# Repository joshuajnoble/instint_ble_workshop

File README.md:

instint_ble_workshop
====================

This is for a workshop I ran at instint 2014 and it has a bunch of components to it:

board: eagle files that I created for the board that we used.
ios: openframeworks applications for running on a BLE compatible IOS device
osx: openframeworks applications for running on a BLE compatible OSX device
processing: processing applications for running on a BLE compatible Android device
rfduino: applications that running on the RFDuino BLE platform

In the workshop we used a few different components:

* https://www.sparkfun.com/products/8680	SoftPot Membrane Potentiometer - 50mm
* https://www.sparkfun.com/products/9873	FTDI Basic Breakout - 3.3V
* https://www.sparkfun.com/products/9264	LED - RGB Diffused Common Cathode
* https://www.sparkfun.com/products/11026	Jumper Wires Standard 7\" M/M Pack of 30
* https://www.sparkfun.com/products/12002	Breadboard - Self-Adhesive (White)
* https://www.sparkfun.com/products/11446	Triple Axis Accelerometer Breakout - ADXL362

And here's what these different applications in the different platforms do:

* sayhi - just says hi back and from the RFDuino to the host device
* changeLED - sends an LED signals to the RFDuino to control an RGB LED
* receiveAcc - receives a accelerometer signal from the rfduino and moves a little ball around on the screen (pretty dull tbh)

There's another one that only run on the RFDuino:

* customID - runs on a device and sends a message to another device
* customIDdevice - runs on a device and sends a message to another device

I have a hacked RFDuino install, so drop that in your Arduino (or Arduino.app) hardware/arduino folder. I also have a hacked Processing Android mode, so drop that in your Processing/modes folder to leverage features in more contemporary Android releases (i.e. v18+). Any questions or problems just open an issue and I'll get back to you ASAP

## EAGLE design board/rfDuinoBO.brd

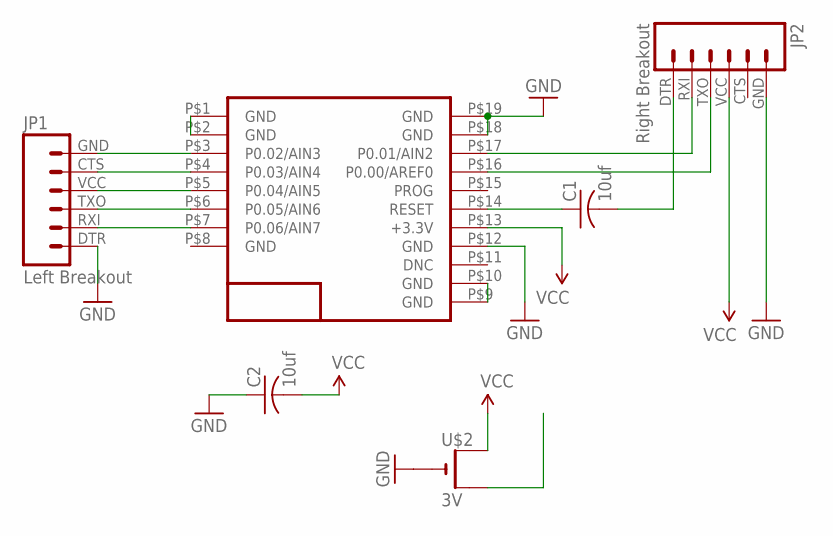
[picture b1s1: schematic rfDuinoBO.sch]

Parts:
C1, C2: 10uf; C0603
JP1: Left Breakout; 1X06
JP2: Right Breakout; 1X06
U$1: RFD22301; RFD21733
U$2: 3V; CR2032-THRU

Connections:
GND: C2.1, JP1.DTR (1), JP2.GND (6), U$1.P$12 (GND), U$1.P$18 (GND), U$1.P$19 (GND), U$2.-
unnamed: U$1.P$9 (GND), U$1.P$10 (GND)
unnamed: U$1.P$1 (GND), U$1.P$2 (GND)
unnamed: C1.1, U$1.P$14 (RESET)
unnamed: C1.2, JP2.DTR (1)
unnamed: JP2.RXI (2), U$1.P$17 (P0.01/AIN2)
unnamed: JP2.TXO (3), U$1.P$16 (P0.00/AREF0)
P2: JP1.GND (6), U$1.P$3 (P0.02/AIN3)
P3: JP1.CTS (5), U$1.P$4 (P0.03/AIN4)
P4: JP1.VCC (4), U$1.P$5 (P0.04/AIN5)
P5: JP1.TXO (3), U$1.P$6 (P0.05/AIN6)
P6: JP1.RXI (2), U$1.P$7 (P0.06/AIN7)
VCC: C2.2, JP2.VCC (4), U$1.P$13 (+3.3V), U$2.+1 (+)

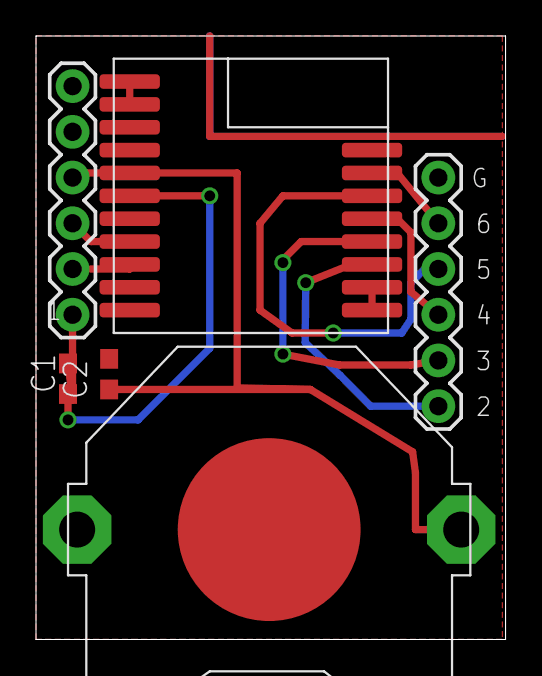
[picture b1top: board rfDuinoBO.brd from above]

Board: 2 copper layers, 26.1 x 33.5 mm, 6 parts (0 on the bottom side), 13 nets.

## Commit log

2014-09-27 adding all osx apps
2014-09-27 cleanup
2014-09-27 readding
2014-09-28 adding board

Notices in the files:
parts and their libraries:
SparkFun-Connectors: Licensing: Creative Commons ShareAlike 4.0 International - https://creativecommons.org/licenses/by-sa/4.0
